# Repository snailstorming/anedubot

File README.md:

# anedubot
Another educational robot

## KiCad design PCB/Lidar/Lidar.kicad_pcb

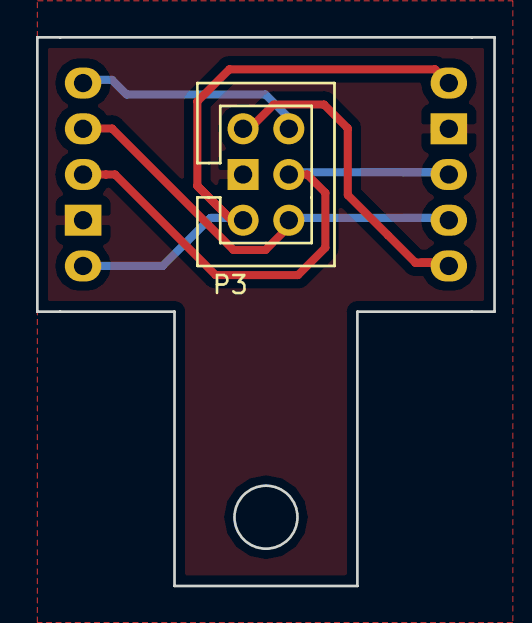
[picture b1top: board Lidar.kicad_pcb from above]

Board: 2 copper layers, 25.4 x 30.5 mm, 3 parts (0 on the bottom side), 6 nets.

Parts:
P1: LIDAR_LEFT; Pin_Header_Straight_1x05
P2: LIDAR_RIGHT; Pin_Header_Straight_1x05
P3: CONN_02X03; Pin_Header_Straight_2x03

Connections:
GND: P1.2, P2.2, P3.4
LID_L_XSHUT: P1.5, P3.5
LID_R_XSHUT: P2.5, P3.6
LID_SCL: P1.4, P2.4, P3.1
LID_SDA: P1.3, P2.3, P3.3
LID_VIN: P1.1, P2.1, P3.2

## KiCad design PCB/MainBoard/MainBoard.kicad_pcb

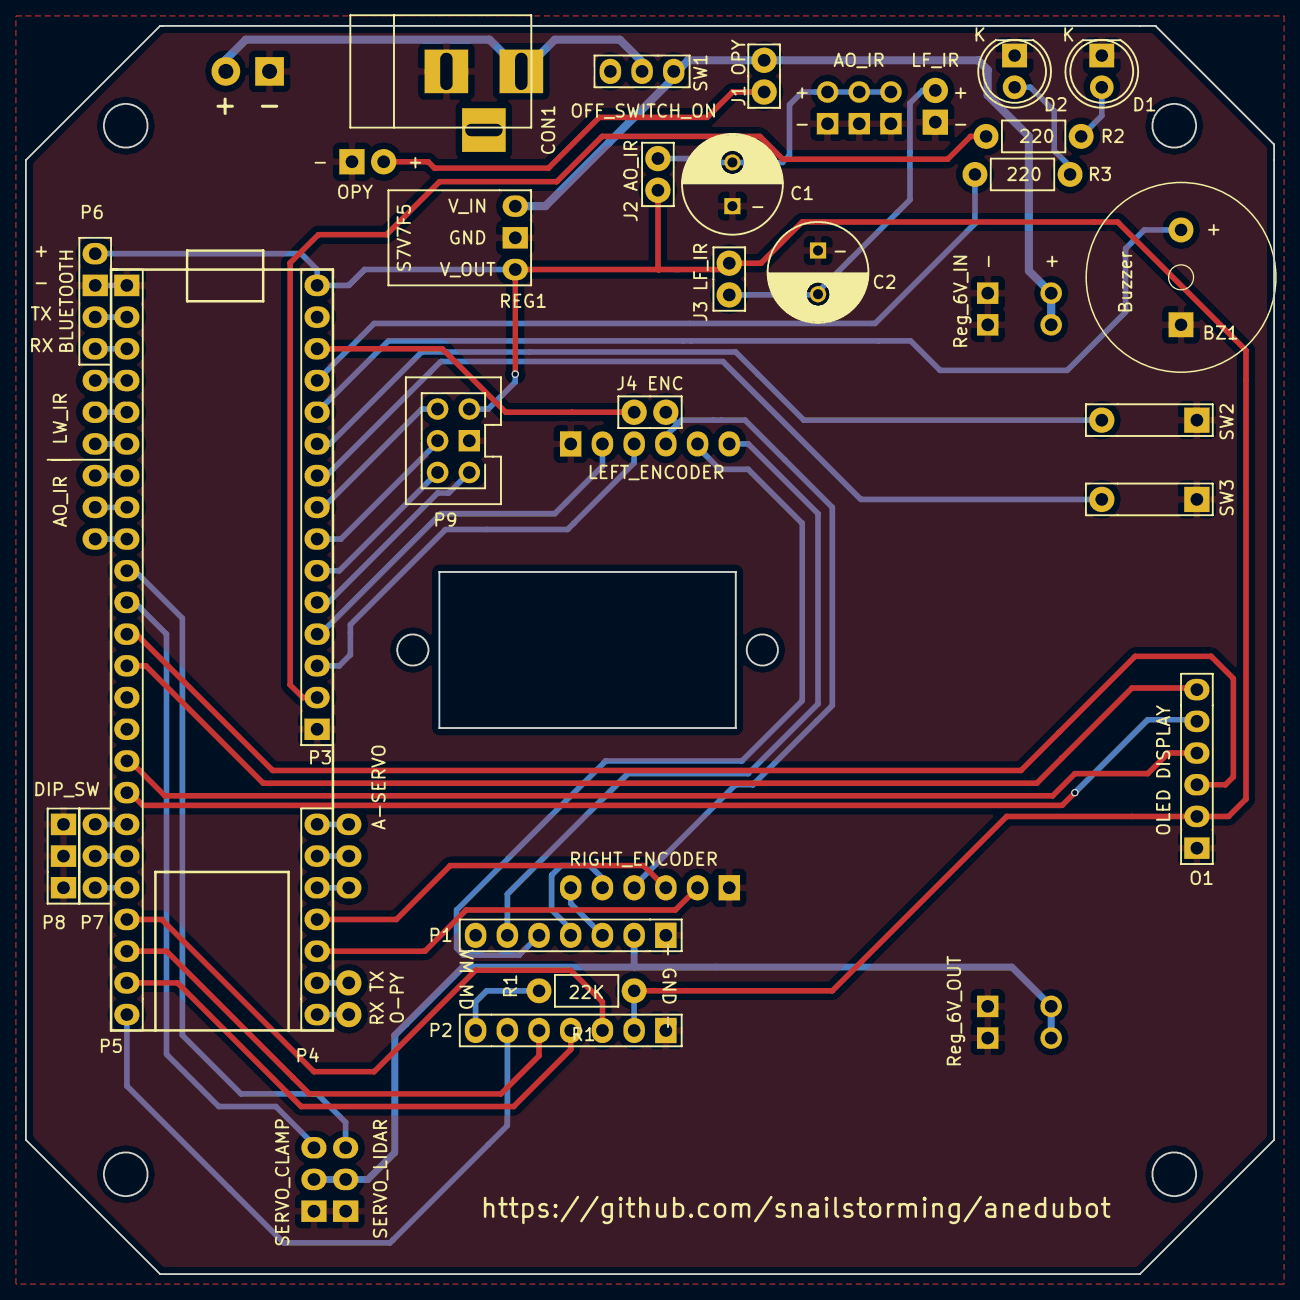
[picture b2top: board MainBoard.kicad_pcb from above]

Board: 2 copper layers, 100.0 x 100.0 mm, 38 parts (0 on the bottom side), 55 nets.

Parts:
BZ1: Buzzer; Buzzer_15x7.5RM7.6
C1, C2: C; C_Radial_D8_L11.5_P3.5
CON1: BARREL_JACK
D1, D2: LED; LED-5MM
J1 OPY: CONN_RASPY; Pin_Header_Straight_1x02
J2 AO_IR, J3 LF_IR, J4 ENC: CONN_01X02; Pin_Header_Straight_1x02
O1: OLED DISPLAY; Pin_Header_Straight_1x06
P1, P2: MOTOR_DRIVER; Pin_Header_Straight_1x07
P4, P5: CONN_01X24; Pin_Header_Straight_1x24
P7: DIP_SW; Pin_Header_Straight_1x03
P8: DIP_SWITCH; Pin_Header_Straight_1x03
P9: CONN_02X03; Pin_Header_Straight_2x03
P10: AO_IR; Pin_Header_Straight_1x02
P11: IR_SENSORS; Pin_Header_Straight_2x03
P12: CONN_RASPY; Pin_Header_Straight_1x02
P13, P21: CONN_01X02; Pin_Header_Straight_1x02
P14: Reg_6V_IN; Pin_Header_Straight_2x02
P15: Reg_6V_OUT; Pin_Header_Straight_2x02
P16: LEFT_ENCODER; Pin_Header_Straight_1x06
P17: RIGHT_ENCODER; Pin_Header_Straight_1x06
P18: SERVO_CLAMP; Pin_Header_Straight_1x03
P19: SERVO_LIDAR; Pin_Header_Straight_1x03
P20: CONN_01X03; Pin_Header_Straight_1x03
P22: AO_IR | LW_IR; Pin_Header_Straight_1x10
R1, R2, R3: R; Resistor_Horizontal_RM7mm
REG1: S7V7F5; Pin_Header_Straight_1x03
SW1: OFF_SWITCH_ON; Pin_Header_Straight_1x03
SW2, SW3: SW_PUSH; Pin_Header_Straight_1x02

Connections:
+5V: J2 AO_IR.1, J3 LF_IR.1, O1.5, P2.6, P4.24, P9.2, P22.10, R1.1, REG1.1
+6V: P1.2, P15.1, P15.2, P18.2, P19.2
+BATT: CON1.1, P13.2, SW1.2
A_EN: P2.3, P5.3
A_PH: P2.2, P5.1
BUTTON_1: P4.19, SW2.2
BUTTON_2: P4.18, SW3.2
B_EN: P2.5, P5.4
B_PH: P2.4, P5.2
D0: O1.4, P5.13
D1: O1.3, P5.9
DC: O1.1, P5.12
GND: BZ1.2, C1.1, C2.1, CON1.2, D1.1, D2.1, O1.6, P1.1, P2.7, P4.10, P5.24, P8.1, P8.2, P8.3, P9.4, P10.1, P11.1, P11.3, P11.5, P12.2, P13.1, P14.3, P14.4, P15.3, P15.4, P16.6, P17.6, P18.3, P19.3, P22.9, REG1.2, SW2.1, SW3.1
GREEN_LED: P4.21, R3.1
L_ENC_A: P4.12, P16.4
L_ENC_B: P4.13, P16.5
unnamed: BZ1.1, D1.2, R2.2
unnamed: C2.2, J3 LF_IR.2, P10.2
unnamed: C1.2, J2 AO_IR.2, P11.2, P11.4, P11.6
unnamed: D2.2, R3.2
unnamed: P2.1, R1.2
unnamed: P4.2, P21.1
unnamed: P4.1, P21.2
unnamed: J1 OPY.1, P14.1, P14.2, REG1.3, SW1.1
unnamed: J1 OPY.2, P12.1
unnamed: P4.5, P20.3
unnamed: P4.6, P20.2
unnamed: P4.7, P20.1
unnamed: J4 ENC.1, P4.22
unnamed: P5.5, P7.1
unnamed: P5.6, P7.2
unnamed: P5.7, P7.3
unnamed: P5.16, P22.1
unnamed: P5.17, P22.2
unnamed: P5.18, P22.3
unnamed: P5.19, P22.4
unnamed: P5.20, P22.5
unnamed: P5.21, P22.6
unnamed: P5.22, P22.7
unnamed: P5.23, P22.8
unnamed: J4 ENC.2, P16.3, P17.3
O1_A: P1.6, P16.1
O1_B: P1.4, P17.2
O2_A: P1.5, P16.2
O2_B: P1.3, P17.1
RED_LED: P4.20, R2.1
RES: O1.2, P5.8
R_ENC_A: P4.4, P17.4
R_ENC_B: P4.3, P17.5
SCL: P4.17, P9.1
SDA: P4.16, P9.3
SERVO_CLAW_PWM: P5.15, P18.1
SERVO_LIDAR_PWM: P5.14, P19.1
X_LEFT: P4.15, P9.5
X_RIGHT: P4.14, P9.6

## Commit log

2017-12-23 adding frame files
2017-12-23 adding lidar PCB
2017-12-23 adding 3D clamp
2017-12-23 adding main pcb board
2017-12-23 adding hardware test code
2017-12-23 Adding photograpy to README
2017-12-24 Adding two libraries
2017-12-24 Create Issues
2017-12-24 Update Issues
2017-12-24 Adding lidar test code
2017-12-28 adding image
2017-12-29 Create Components
2017-12-29 Rename Components to Components.md
2017-12-29 Add images
2018-01-01 improving silks layers in PCB
2018-01-01 Add PCB v2
    Add PCB with improved silk layers
2018-01-01 Improving PCB silks layers
2018-01-02 fix mistake in f.silk PCB
2018-01-02 Update PCB price
2018-01-03 Add stl files
2018-01-04 Correct a mistake in PCB silk layer
2018-01-04 Add: Building folder
2018-01-04 Rename Building_Main_PCB.md to 2 Building_Main_PCB.md
2018-01-04 Rename Building_Base.md to 1 Building_Base.md
2018-01-04 Rename 1 Building_Base.md to 1_Building_Base.md
2018-01-04 Rename 2 Building_Main_PCB.md to 2_Building_Main_PCB.md
2018-01-05 Improve: Lidar PCB silk
2018-01-05 Create 4_Building_Lidar
2018-01-05 Rename 4_Building_Lidar to 4_Building_Lidar.md
2018-01-06 Add Teensy code: Hello_anedu
2018-01-07 Change Red Led connection in main PCB
2018-01-07 Programing hello_anuedu
2018-02-01 add test anedu
2018-02-01 modify test anedu
2018-02-03 Change test_Anedubot
2018-02-03 Changes in test_Anedubot
2018-02-04 Add lidarArrow
2018-02-07 change test_Aneduot
2018-02-09 Change lidar PCB
2018-02-24 Change test_anedu
